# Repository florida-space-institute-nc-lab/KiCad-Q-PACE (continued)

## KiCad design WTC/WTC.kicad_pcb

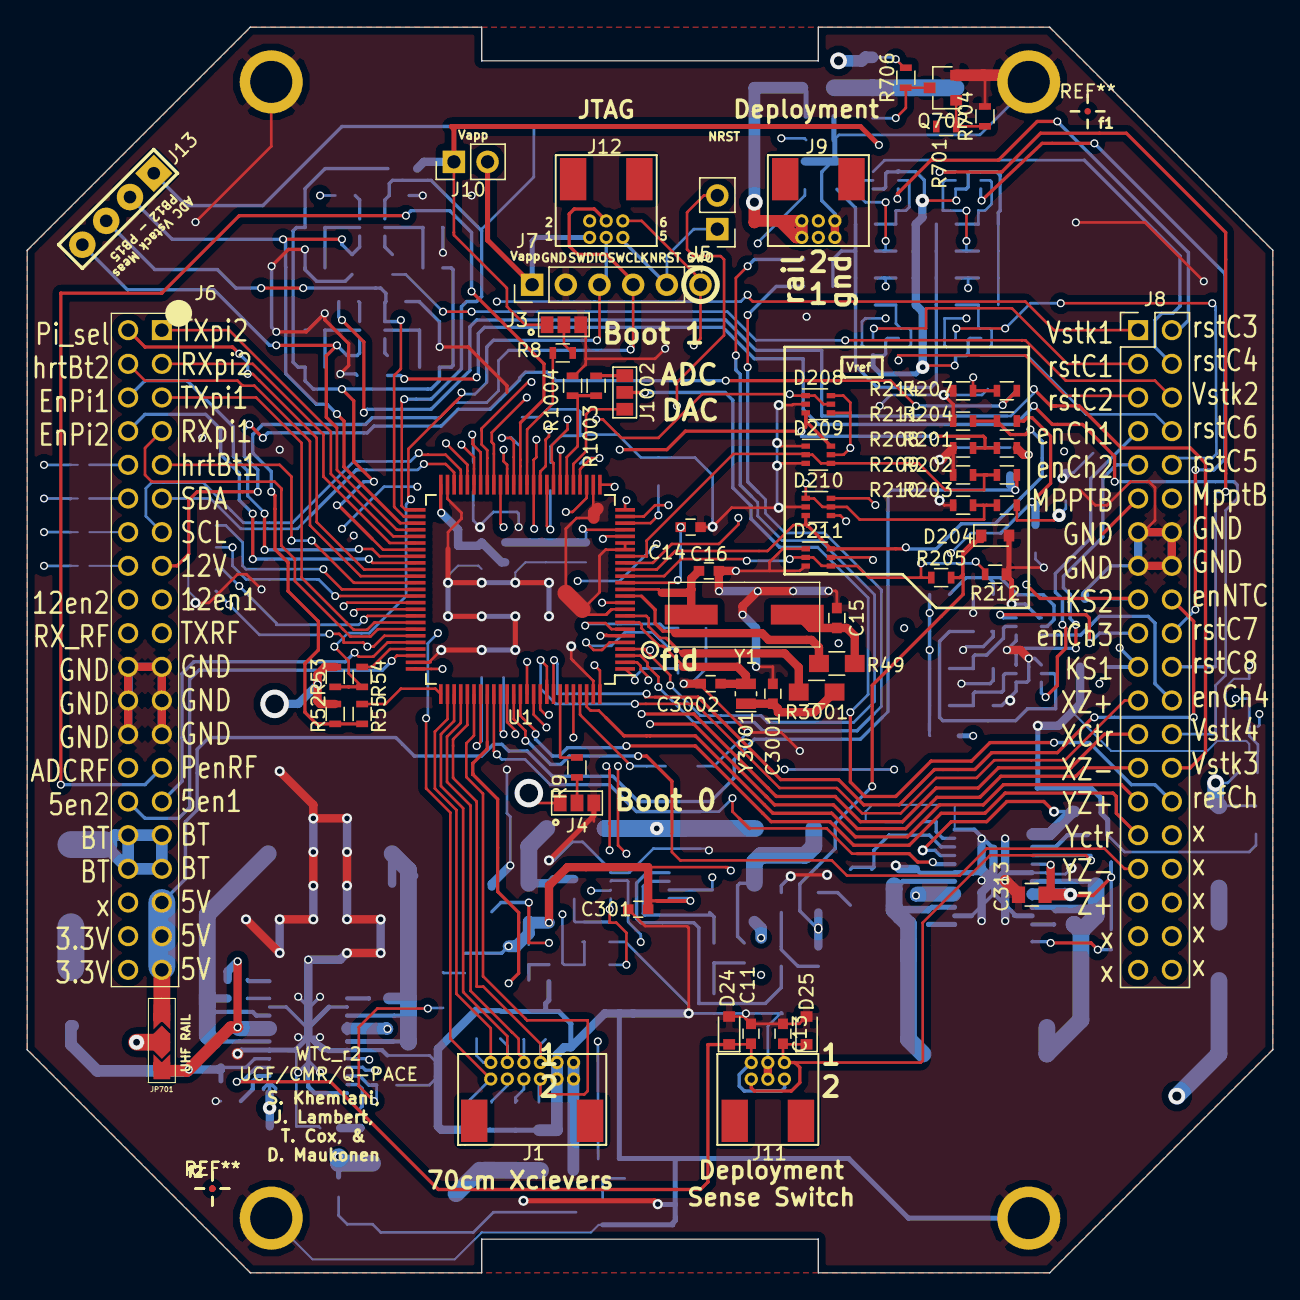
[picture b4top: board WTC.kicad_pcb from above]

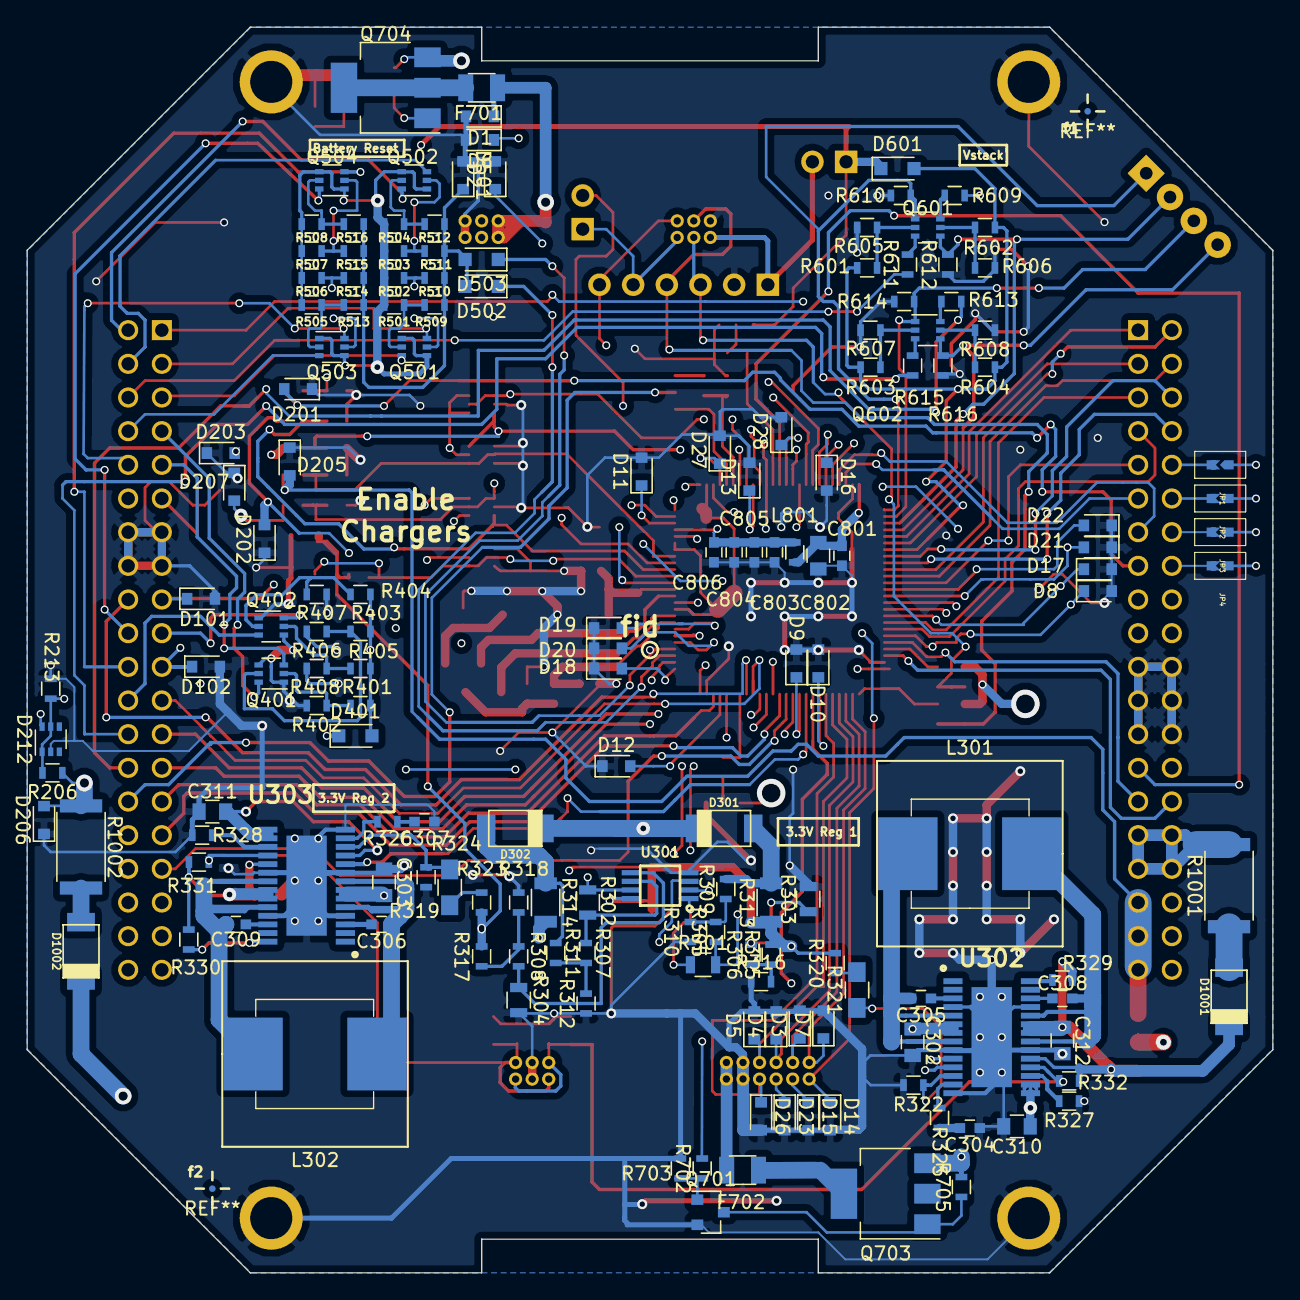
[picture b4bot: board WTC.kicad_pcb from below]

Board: 4 copper layers, 94.0 x 94.0 mm, 227 parts (163 on the bottom side), 190 nets.

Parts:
C11, C13, C14, C301, C305, C306, C308, C309, C801, C804, C805: 0.1 uF; C_0603
C15, C16: 30pF; C_0603
C302, C303, C312, C313: 10 uF; C_0805
C304, C307: 680pF; C_0603
C310, C311: 4.7 uF; C_0805
C802: 1 uF; C_0805
C803: 1 uF; C_0603
C806: 180 pF; C_0603
C3001, C3002: 4.5pF; C_0603
D1, D2, D3, D4, D5, D6, D7, D8, D9, D10, D11, D12, D13, D14, D15, D16, D17, D18, D19, D20, D21, D22, D23, D24, D25, D26, D27, D28, D101, D102, D201, D202, D203, D204, D205, D206, D207, D501: D_TVS_ALT; D_0805
D208, D209, D210, D211, D212: Diode_3_Switching; SOT-363_SC-70-6
D301, D302: D_Schottky_Small; SOD-128
D401, D502, D503, D601: D_Small_ALT; D_SOD-323_HandSoldering
D1001, D1002: D_Schottky_ALT; SOD-128
F701, F702: 3A; Fuse_SMD1206_Reflow
J1: 70cm_Primary; G125-MH11205L3P
J2: Pin_Header_Straight_1x02_Pitch2.54mm
J3: Boot1; GS3
J4: Boot0; GS3
J5: SWD; Pin_Header_Straight_1x01_Pitch2.54mm-rnd
J6: Main 40 Pin Stacking Avionics Interconnect - r 4; Samtec_SSQ-120-03-G-D_QPACE_40-Pin
J7: CONN_01X05; Pin_Header_Straight_1x05_Pitch2.54mm
J8: WTC/MPPT/BP&C_Interconnect_r0; Pin_Header_Straight_2x20_Pitch2.54mm
J9: Deployment; G125-MH10605L3P
J10: CONN_01X02; Pin_Header_Straight_1x02_Pitch2.54mm
J11: CONN_02X03; G125-MH10605L3P
J12: SWD Gecko; G125-MH10605L3P
J13: CONN_01X04; 01x04
J1002: GS3
JP1, JP2, JP3, JP4: SolderBridge_Arrow_small
JP701: UHF Rail Select; SolderBridge_2_way_NP
L301, L302: 3.3 uH; 3.3uH_Dual
L801: Ferrite; L_0603
P3001: Mounting; Mounting_Drill
P3002, P3003, P3004: VAL**; Mounting_Drill
Q401, Q402, Q601, Q602: BSS138_Dual; SOT-363_SC-70-6
Q501, Q502, Q503, Q504: Q_PMOS_SDG_Dual; SOT-363_SC-70-6
Q701, Q702: BSS138; SOT-23
Q703, Q704: Q_PMOS_GDS; SOT-223-3Lead_TabPin2_ONE_2
R8, R9: 100k; R_0603
R49, R319, R321, R3001: 0; R_0805_HandSoldering
R52, R53, R610, R612, R614, R616, R701, R702: 4.99K; R_0603
R54, R55: 51; R_0603
R201, R202, R203, R204, R205, R207, R509, R510, R511, R512, R513, R514, R515, R516, R601, R602, R603, R604: 10K; R_0603
R206: 10M; R_0603
R208: 1k; R_0603
R209: 1K; R_0603
R210, R211, R212: 2.49K; R_0603
R213, R305, R306, R307, R308, R402, R406, R407, R408, R605, R606, R607, R608, R1003, R1004: 1M; R_0603
R214: 523; R_0603
R301, R302, R303, R304: 20M; R_0805
R309, R310, R311, R312, R315, R316, R317, R318: 499K 1%; R_0603
R313, R314: 0.1; R_1206
R320, R323: 352K; R_0603
R322, R324, R329, R330, R331, R332, R401, R403, R404, R405, R501, R502, R503, R504, R505, R506, R507, R508, R703, R704, R705, R706: 100K; R_0603
R325, R326: 78.7K; R_0603
R327, R328: 105K; R_0603
R609, R611, R613, R615: 49.9K; R_0603
R1001, R1002: 0.1; R_2512
U1: STM32L151VE; LQFP-100_14x14mm_Pitch0.5mm
U301: LPV812; VSSOP8_P0.65mm_W3mm
U302, U303: LTC3119; LTC3119_29
Y1: 16 MHz; ECS-160-20-5PXDU-TR_16MHz_Crystal
Y3001: 32.768 KHz; Crystal_SMD_MicroCrystal_CC8V-T1A-2pin_2.0x1.2mm

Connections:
3.3Raw-1: C301.1, C302.1, D202.2, R204.2, R313.1, R315.2, R320.2, U301.8, U302.6, U302.7
3.3Raw-2: C303.2, D204.1, R205.2, R314.1, R317.2, R323.2, U303.6, U303.7
3_3V_Rail: C801.1, C802.1, D207.2, D208.4, D208.6, D209.5, D210.4, D210.6, D211.5, D212.6, D301.1, D302.1, D401.1, D601.1, J3.1, J4.1, J6.38, J6.40, J10.1, L801.2, Q501.1, Q501.4, Q502.1, Q502.4, Q503.1, Q503.4, Q504.1, Q504.4, R52.2, R53.2, R203.2, R501.1, R502.1, R503.1, R504.1, R505.1, R506.1, R507.1, R508.1, U1.6, U1.11, U1.21, U1.28, U1.50, U1.75, U1.100
5V_Rail: D205.2, J6.35, J6.37, J6.39, JP701.1, R202.2
5V_Rail_1_Enable: J6.29, U1.71
5V_Rail_2_Enable: J6.30, U1.73
5X_Out_1: D210.1, D210.5, R203.1, R210.2, U1.17
5X_Out_2: D210.3, D211.6, R204.1, R211.2, U1.16
5X_Out_3: D211.2, D211.4, R205.1, R212.2, U1.15
10X_Out_1: D209.2, D209.4, R202.1, R209.2, U1.18
10X_Out_2: D208.3, D209.6, R201.1, R208.2, U1.32
12V_1_Enable: J6.17, U1.65
12V_2_Enable: J6.18, U1.66
12V_Rail: D201.2, J6.15, R207.2
20X_Out_1: D208.1, D208.5, R207.1, R214.2, U1.33
70cm_AUX_ADC: D14.1, J1.12, U1.41
70cm_AUX_GPIO: D7.1, J1.11, U1.77
70cm_Primary_Enable: D5.1, J1.5, U1.80
70cm_Primary_UART_RX: D4.1, J1.7, U1.79
70cm_Primary_UART_TX: D3.1, J1.9, U1.78
70cm_Secondary_Enable: D26.1, J1.6, U1.81
/Boot0_Sel.: R9.1, U1.94
/JTG1: J7.1, J10.2, J12.1
/JTG3: J7.3, J12.3, R53.1, R54.2
/JTG4: J7.4, J12.4, R52.1, R55.2
/SWCLK: R55.1, U1.76
/SWDIO: R54.1, U1.72
ADC_REF_Chrg: R1003.2, R1004.1, U1.31
Battery_Rail: D203.2, J6.31, J6.32, J6.33, J6.34, Q704.3, R201.2, R706.2, R1001.2
Battery_Reset_1: D502.1, U1.3
Battery_Reset_2: D503.1, U1.4
DAC_REF_Chrg: J1002.1, U1.30
Deployment_Battery_Rail: D1.1, F701.2, J9.1, J9.2
EN_Chrg_1: J8.7, Q401.6
EN_Chrg_2: J8.9, Q401.3
EN_Chrg_3: J8.19, Q402.6
EN_Chrg_4: J8.24, Q402.3
EN_MPPT_XCtr: J8.25, U1.91
EN_MPPT_XZ+: J8.23, U1.92
EN_MPPT_XZ-: J8.27, U1.90
EN_MPPT_YCtr: J8.31, U1.88
EN_MPPT_YZ+: J8.29, U1.98
EN_MPPT_YZ-: J8.33, U1.87
EN_MPPT_Z+: J8.35, U1.86
EN_NTC_Drive: J8.18, U1.93
GND: C11.1, C13.1, C14.2, C15.1, C16.1, C301.2, C302.2, C303.1, C304.2, C307.2, C310.2, C311.2, C312.2, C313.1, C801.2, C802.2, C803.2, C804.2, C805.2, C806.2, C3001.2, C3002.2, D1.2, D2.2, D3.2, D4.2, D5.2, D6.2, D7.2, D8.2, D9.2, D10.2, D11.2, D12.1, D13.2, D14.2, D15.2, D16.2, D17.2, D18.1, D19.1, D20.1, D21.1, D22.1, D23.2, D24.2, D25.2, D26.2, D27.2, D28.2, D101.2, D102.2, D201.1, D202.1, D203.1, D204.2, D205.1, D206.1, D207.1, D208.2, D209.1, D209.3, D210.2, D211.1, D211.3, D212.2, D501.2, J1.3, J1.4, J3.3, J4.3, J6.21, J6.22, J6.23, J6.24, J6.25, J6.26, J7.2, J8.13, J8.14, J8.15, J8.16, J9.5, J9.6, J11.3, J11.4, J12.2, P3001.1, P3002.1, P3003.1, P3004.1, Q401.1, Q401.4, Q402.1, Q402.4, Q701.2, Q702.2, R208.1, R209.1, R210.1, R211.1, R212.1, R213.1, R214.1, R303.2, R304.2, R310.1, R312.1, R316.1, R318.1, R322.1, R324.1, R327.1, R328.1, R402.2, R406.2, R407.2, R408.2, R605.1, R606.1, R607.1, R608.1, R610.1, R612.1, R614.1, R616.1, R703.2, R704.2, R1004.2, U1.10, U1.19, U1.20, U1.27, U1.49, U1.74, U1.99, U301.4, U302.4, U302.9, U302.14, U302.20, U302.25, U302.29, U303.4, U303.9, U303.14, U303.20, U303.25, U303.29
I2C_SCL: J6.13, U1.47
I2C_SDA: J6.11, U1.48
Imon_3.3-1: R301.1, U1.36, U301.1
Imon_3.3-2: R302.1, U1.35, U301.7
Kill_Switch_1: D102.1, J8.21, U1.45
Kill_Switch_2: D101.1, J8.17, U1.46
MPPT_BUS: D206.2, J8.11, J8.12, R206.1, R1002.2
MPPT_BUS_MON: D212.1, D212.5, R206.2, R213.2, U1.24
NRST: J2.1, J7.5, J12.5
unnamed: C14.1, J2.2, U1.14
unnamed: C15.2, R49.2, Y1.1
unnamed: C16.2, U1.13, Y1.2
unnamed: C304.1, R325.1
unnamed: C305.1, U302.3
unnamed: C305.2, L301.1, U302.5, U302.8
unnamed: C306.1, U303.3
unnamed: C306.2, L302.1, U303.5, U303.8
unnamed: C307.1, R326.1
unnamed: C308.1, L301.2, U302.21, U302.24
unnamed: C308.2, U302.26
unnamed: C309.1, L302.2, U303.21, U303.24
unnamed: C309.2, U303.26
unnamed: C310.1, U302.11, U302.15, U302.16
unnamed: C311.1, U303.11, U303.15, U303.16
unnamed: C3001.1, R3001.1, Y3001.1
unnamed: C3002.1, U1.8, Y3001.2
unnamed: D301.2, R309.2, R313.2
unnamed: D302.2, R311.2, R314.2
unnamed: D501.1, D502.2, D503.2, R509.2, R510.2, R511.2, R512.2, R513.2, R514.2, R515.2, R516.2
unnamed: D1001.2, R1001.1
unnamed: D1002.2, R1002.1
unnamed: F701.1, Q704.2
unnamed: F702.1, Q703.2
unnamed: J3.2, R8.2
unnamed: J4.2, R9.2
unnamed: J6.10, JP1.1
unnamed: J6.12, JP2.1
unnamed: J6.14, JP3.1
unnamed: J6.16, JP4.1
unnamed: J5.1, J12.6, U1.89
unnamed: J1002.3, R1003.1
unnamed: JP701.2, Q703.3, R705.1
unnamed: Q401.2, R401.1, R402.1
unnamed: Q401.5, R403.1, R406.1
unnamed: Q402.2, R404.1, R407.1
unnamed: Q402.5, R405.1, R408.1
unnamed: Q501.2, R501.2, R509.1
unnamed: Q501.5, R502.2, R510.1
unnamed: Q502.2, R503.2, R511.1
unnamed: Q502.5, R504.2, R512.1
unnamed: Q503.2, R505.2, R513.1
unnamed: Q503.5, R506.2, R514.1
unnamed: Q504.2, R507.2, R515.1
unnamed: Q504.5, R508.2, R516.1
unnamed: Q601.2, R601.1, R605.2
unnamed: Q601.3, R611.1
unnamed: Q601.5, R602.1, R606.2
unnamed: Q601.6, R609.1
unnamed: Q602.2, R603.1, R607.2
unnamed: Q602.3, R615.1
unnamed: Q602.5, R604.1, R608.2
unnamed: Q602.6, R613.1
unnamed: Q701.1, R702.1, R703.1
unnamed: Q701.3, Q703.1, R705.2
unnamed: Q702.1, R701.1, R704.1
unnamed: Q702.3, Q704.1, R706.1
unnamed: R8.1, U1.37
unnamed: R49.1, U1.12
unnamed: R301.2, R305.2, U301.2
unnamed: R302.2, R307.2, U301.6
unnamed: R303.1, R306.2, U301.3
unnamed: R304.1, R308.2, U301.5
unnamed: R305.1, R309.1, R310.2
unnamed: R306.1, R315.1, R316.2
unnamed: R307.1, R311.1, R312.2
unnamed: R308.1, R317.1, R318.2
unnamed: R319.1, R323.1
unnamed: R319.2, R324.2, U303.12
unnamed: R320.1, R321.2
unnamed: R321.1, R322.2, U302.12
unnamed: R325.2, U302.13
unnamed: R326.2, U303.13
unnamed: R327.2, U302.17
unnamed: R328.2, U303.17
unnamed: R329.2, U302.28
unnamed: R330.2, U303.28
unnamed: R3001.2, U1.9
Pgood_3.3-1: U1.83, U302.10
Pgood_3.3-2: U1.84, U303.10
Pi_Heartbeat_Pi1: J6.9, U1.62
Pi_Heartbeat_Pi2: J6.4, U1.61
PwrMon_RF_ADC: J6.28, U1.40
Pwr_En_Pi1: J6.6, U1.58
Pwr_En_Pi2: J6.8, U1.59
REF_Chrg: J8.30, J1002.2
RF_Deck_Power_Enable: J6.27, U1.38
Reset_C1: J8.3, Q501.6
Reset_C2: J8.5, Q501.3
Reset_C3: J8.2, Q502.6
Reset_C4: J8.4, Q502.3
Reset_C5: J8.10, Q503.6
Reset_C6: J8.8, Q503.3
Reset_C7: J8.20, Q504.6
Reset_C8: J8.22, Q504.3
STM_PA0: D11.1, U1.23
STM_PA4: D27.1, U1.29
STM_PA8: D17.1, JP3.2, U1.67
STM_PA11: D8.1, JP4.2, U1.70
STM_PC5_ADC: D13.1, U1.34
STM_PC6: D22.2, JP1.2, U1.63
STM_PC7: D21.2, JP2.2, U1.64
STM_PC13: D19.2, U1.7
STM_PD1: D10.1, U1.82
STM_PD4: D9.1, U1.85
STM_PE1: D12.2, U1.97
STM_PE2: D18.2, U1.1
STM_PE6: D20.2, U1.5
STM_PE8: D28.1, U1.39
STM_PE13: D16.1, U1.44
Spacecraft_Deployment_Switch_1: C11.2, D24.1, J11.2, J11.5, R332.2, U302.18
Spacecraft_Deployment_Switch_2: C13.2, D25.1, J11.1, J11.6, R331.2, U303.18
UART_RXD_Pi1: J6.7, U1.69
UART_RXD_Pi2: J6.3, U1.56
UART_RX_UHF_Sec: D23.1, J1.8, J6.20, U1.26
UART_TXD_Pi1: J6.5, U1.68
UART_TXD_Pi2: J6.1, U1.55
UART_TX_UHF_Sec: D15.1, J1.10, J6.19, U1.25
UHF_Deploy_1: D2.1, J9.3, U1.43
UHF_Deploy_2: D6.1, J9.4, U1.42
UHF_Power_Enable: R702.2, U1.96
UHF_Rail: F702.2, J1.1, J1.2
UHF_Rail_Raw: C312.1, C313.2, D1001.1, D1002.1, JP701.3, R329.1, R330.1, R331.1, R332.1, U302.19, U302.22, U302.23, U303.19, U303.22, U303.23
VDDA: C803.1, C804.1, C805.1, C806.1, L801.1, U1.22
V_Stack_1: J8.1, R609.2
V_Stack_1_Meas: J13.1, Q601.1, R610.2, U1.51
V_Stack_2: J8.6, R611.2
V_Stack_2_Meas: J13.2, Q601.4, R612.2, U1.53
V_Stack_3: J8.28, R613.2
V_Stack_3_Meas: J13.3, Q602.1, R614.2, U1.52
V_Stack_4: J8.26, R615.2
V_Stack_4_Meas: J13.4, Q602.4, R616.2, U1.54
WTC_BUS_Switch_Pi_Select: J6.2, U1.60
WTC_EN_Chrg: D401.2, R401.2, R403.2, R404.2, R405.2, U1.2
WTC_V_Stack: D601.2, R601.2, R602.2, R603.2, R604.2, U1.57

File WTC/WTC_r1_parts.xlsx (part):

WTC_r2
Ref. | Value | Footprint | Type | Side
C305 | 0.1 uF | Capacitors_SMD:C_0603 | C | bottom
C306 | 0.1 uF | Capacitors_SMD:C_0603 | C | bottom
C308 | 0.1 uF | Capacitors_SMD:C_0603 | C | bottom
C309 | 0.1 uF | Capacitors_SMD:C_0603 | C | bottom
C801 | 0.1 uF | Capacitors_SMD:C_0603 | C | bottom
C804 | 0.1 uF | Capacitors_SMD:C_0603 | C | bottom
C805 | 0.1 uF | Capacitors_SMD:C_0603 | C | bottom
C802 | 1 uF | Capacitors_SMD:C_0805 | C | bottom
C803 | 1 uF | Capacitors_SMD:C_0603 | C | bottom
C302 | 10 uF | Capacitors_SMD:C_0805 | C | bottom
C303 | 10 uF | Capacitors_SMD:C_0805 | C | bottom
C312 | 10 uF | Capacitors_SMD:C_0805 | C | bottom
C806 | 180 pF | Capacitors_SMD:C_0603 | C | bottom
C310 | 4.7 uF | Capacitors_SMD:C_0805 | C | bottom
C311 | 4.7 uF | Capacitors_SMD:C_0805 | C | bottom
C304 | 680pF | Capacitors_SMD:C_0603 | C | bottom
C307 | 680pF | Capacitors_SMD:C_0603 | C | bottom
D502 | 1N4148WS | Footprints:D_SOD-323F-2 | D | bottom
D503 | 1N4148WS | Footprints:D_SOD-323F-2 | D | bottom
D601 | 1N4148WS | Footprints:D_SOD-323F-2 | D | bottom
D212 | BAS16VY,115 | TO_SOT_Packages_SMD:SOT-363_SC-70-6 | D | bottom
D301 | PMEG3050EP,115 | SH_SOD_SON_SOT:SOD-128 | D | bottom
D302 | PMEG3050EP,115 | SH_SOD_SON_SOT:SOD-128 | D | bottom
F701 | 3A / PTTC | Fuse_Holders_and_Fuses:Fuse_SMD1206_Reflow | F | bottom
F702 | 3A / PTTC | Fuse_Holders_and_Fuses:Fuse_SMD1206_Reflow | F | bottom
L301 | DRA125-3R3-R | Footprints:3.3uH_Dual | L | bottom
L302 | DRA125-3R3-R | Footprints:3.3uH_Dual | L | bottom
L801 | MPZ1608S300A | Inductors_SMD:L_0603 | L | bottom
Q701 | BSS138 | TO_SOT_Packages_SMD:SOT-23 | Q | bottom
Q401 | BSS138BKS,115 | TO_SOT_Packages_SMD:SOT-363_SC-70-6 | Q | bottom
Q402 | BSS138BKS,115 | TO_SOT_Packages_SMD:SOT-363_SC-70-6 | Q | bottom
Q601 | BSS138BKS,115 | TO_SOT_Packages_SMD:SOT-363_SC-70-6 | Q | bottom
Q602 | BSS138BKS,115 | TO_SOT_Packages_SMD:SOT-363_SC-70-6 | Q | bottom
Q501 | DMP2200UDW-7 | TO_SOT_Packages_SMD:SOT-363_SC-70-6 | Q | bottom
Q502 | DMP2200UDW-7 | TO_SOT_Packages_SMD:SOT-363_SC-70-6 | Q | bottom
Q503 | DMP2200UDW-7 | TO_SOT_Packages_SMD:SOT-363_SC-70-6 | Q | bottom
Q504 | DMP2200UDW-7 | TO_SOT_Packages_SMD:SOT-363_SC-70-6 | Q | bottom
Q703 | NTF6P02T3G | Footprints:SOT-223-3Lead_TabPin2_ONE_2 | Q | bottom
Q704 | NTF6P02T3G | Footprints:SOT-223-3Lead_TabPin2_ONE_2 | Q | bottom
R319 | 0 | Resistors_SMD:R_0805_HandSoldering | R | bottom
R321 | 0 | Resistors_SMD:R_0805_HandSoldering | R | bottom
R1001 | 0.1 | Resistors_SMD:R_2512 | R | bottom
R1002 | 0.1 | Resistors_SMD:R_2512 | R | bottom
R313 | 0.1 | Resistors_SMD:R_1206 | R | bottom
R314 | 0.1 | Resistors_SMD:R_1206 | R | bottom
R322 | 100K | Resistors_SMD:R_0603 | R | bottom
R324 | 100K | Resistors_SMD:R_0603 | R | bottom
R329 | 100K | Resistors_SMD:R_0603 | R | bottom
R330 | 100K | Resistors_SMD:R_0603 | R | bottom
R331 | 100K | Resistors_SMD:R_0603 | R | bottom
R332 | 100K | Resistors_SMD:R_0603 | R | bottom
R401 | 100K | Resistors_SMD:R_0603 | R | bottom
R403 | 100K | Resistors_SMD:R_0603 | R | bottom
R404 | 100K | Resistors_SMD:R_0603 | R | bottom
R405 | 100K | Resistors_SMD:R_0603 | R | bottom
R501 | 100K | Resistors_SMD:R_0603 | R | bottom
R502 | 100K | Resistors_SMD:R_0603 | R | bottom
R503 | 100K | Resistors_SMD:R_0603 | R | bottom
R504 | 100K | Resistors_SMD:R_0603 | R | bottom
R505 | 100K | Resistors_SMD:R_0603 | R | bottom
R506 | 100K | Resistors_SMD:R_0603 | R | bottom
R507 | 100K | Resistors_SMD:R_0603 | R | bottom
R508 | 100K | Resistors_SMD:R_0603 | R | bottom
R703 | 100K | Resistors_SMD:R_0603 | R | bottom
R705 | 100K | Resistors_SMD:R_0603 | R | bottom
R327 | 105K | Resistors_SMD:R_0603 | R | bottom
R328 | 105K | Resistors_SMD:R_0603 | R | bottom
R509 | 10K | Resistors_SMD:R_0603 | R | bottom
R510 | 10K | Resistors_SMD:R_0603 | R | bottom
R511 | 10K | Resistors_SMD:R_0603 | R | bottom
R512 | 10K | Resistors_SMD:R_0603 | R | bottom
R513 | 10K | Resistors_SMD:R_0603 | R | bottom
R514 | 10K | Resistors_SMD:R_0603 | R | bottom
R515 | 10K | Resistors_SMD:R_0603 | R | bottom
R516 | 10K | Resistors_SMD:R_0603 | R | bottom
R601 | 10K | Resistors_SMD:R_0603 | R | bottom
R602 | 10K | Resistors_SMD:R_0603 | R | bottom
R603 | 10K | Resistors_SMD:R_0603 | R | bottom
R604 | 10K | Resistors_SMD:R_0603 | R | bottom
R206 | 10M | Resistors_SMD:R_0603 | R | bottom
R213 | 1M | Resistors_SMD:R_0603 | R | bottom
R305 | 1M | Resistors_SMD:R_0603 | R | bottom
R306 | 1M | Resistors_SMD:R_0603 | R | bottom
R307 | 1M | Resistors_SMD:R_0603 | R | bottom
R308 | 1M | Resistors_SMD:R_0603 | R | bottom
R402 | 1M | Resistors_SMD:R_0603 | R | bottom
R406 | 1M | Resistors_SMD:R_0603 | R | bottom
R407 | 1M | Resistors_SMD:R_0603 | R | bottom
R408 | 1M | Resistors_SMD:R_0603 | R | bottom
R605 | 1M | Resistors_SMD:R_0603 | R | bottom
R606 | 1M | Resistors_SMD:R_0603 | R | bottom
R607 | 1M | Resistors_SMD:R_0603 | R | bottom
R608 | 1M | Resistors_SMD:R_0603 | R | bottom
R301 | 20M | Resistors_SMD:R_0805 | R | bottom
R302 | 20M | Resistors_SMD:R_0805 | R | bottom
R303 | 20M | Resistors_SMD:R_0805 | R | bottom
R304 | 20M | Resistors_SMD:R_0805 | R | bottom
R320 | 352K | Resistors_SMD:R_0603 | R | bottom
R323 | 352K | Resistors_SMD:R_0603 | R | bottom
R610 | 4.99K | Resistors_SMD:R_0603 | R | bottom
R612 | 4.99K | Resistors_SMD:R_0603 | R | bottom
R614 | 4.99K | Resistors_SMD:R_0603 | R | bottom
R616 | 4.99K | Resistors_SMD:R_0603 | R | bottom
R702 | 4.99K | Resistors_SMD:R_0603 | R | bottom
R609 | 49.9K | Resistors_SMD:R_0603 | R | bottom
R611 | 49.9K | Resistors_SMD:R_0603 | R | bottom
R613 | 49.9K | Resistors_SMD:R_0603 | R | bottom
R615 | 49.9K | Resistors_SMD:R_0603 | R | bottom
R309 | 499K 1% | Resistors_SMD:R_0603 | R | bottom
R310 | 499K 1% | Resistors_SMD:R_0603 | R | bottom
R311 | 499K 1% | Resistors_SMD:R_0603 | R | bottom
R312 | 499K 1% | Resistors_SMD:R_0603 | R | bottom
R315 | 499K 1% | Resistors_SMD:R_0603 | R | bottom
R316 | 499K 1% | Resistors_SMD:R_0603 | R | bottom
R317 | 499K 1% | Resistors_SMD:R_0603 | R | bottom
R318 | 499K 1% | Resistors_SMD:R_0603 | R | bottom
R325 | 78.7K | Resistors_SMD:R_0603 | R | bottom
R326 | 78.7K | Resistors_SMD:R_0603 | R | bottom
U301 | LPV812DGKR | Footprints:VSSOP8_P0.65mm_W3mm | U | bottom
U302 | LTC3119 | Footprints:LTC3119_29 | U | bottom
U303 | LTC3119 | Footprints:LTC3119_29 | U | bottom
C11 | 0.1 uF | Capacitors_SMD:C_0603 | C | top
C13 | 0.1 uF | Capacitors_SMD:C_0603 | C | top
C14 | 0.1 uF | Capacitors_SMD:C_0603 | C | top
C301 | 0.1 uF | Capacitors_SMD:C_0603 | C | top
C313 | 10 uF | Capacitors_SMD:C_0805 | C | top
C15 | 30pF | Capacitors_SMD:C_0603 | C | top
C16 | 30pF | Capacitors_SMD:C_0603 | C | top
C3001 | 4.5pF | Capacitors_SMD:C_0603 | C | top
C3002 | 4.5pF | Capacitors_SMD:C_0603 | C | top
D208 | BAS16VY,115 | TO_SOT_Packages_SMD:SOT-363_SC-70-6 | D | top
D209 | BAS16VY,115 | TO_SOT_Packages_SMD:SOT-363_SC-70-6 | D | top
D210 | BAS16VY,115 | TO_SOT_Packages_SMD:SOT-363_SC-70-6 | D | top
D211 | BAS16VY,115 | TO_SOT_Packages_SMD:SOT-363_SC-70-6 | D | top
Q702 | BSS138 | TO_SOT_Packages_SMD:SOT-23 | Q | top
R3001 | 0 | Resistors_SMD:R_0805_HandSoldering | R | top
R49 | 0 | Resistors_SMD:R_0805_HandSoldering | R | top
R54 | 51 | Resistors_SMD:R_0603 | R | top
R55 | 51 | Resistors_SMD:R_0603 | R | top
R214 | 523 | Resistors_SMD:R_0603 | R | top
R704 | 100K | Resistors_SMD:R_0603 | R | top
R706 | 100K | Resistors_SMD:R_0603 | R | top
R8 | 100k | Resistors_SMD:R_0603 | R | top
R9 | 100k | Resistors_SMD:R_0603 | R | top
R201 | 10K | Resistors_SMD:R_0603 | R | top
R202 | 10K | Resistors_SMD:R_0603 | R | top
R203 | 10K | Resistors_SMD:R_0603 | R | top
R204 | 10K | Resistors_SMD:R_0603 | R | top
R205 | 10K | Resistors_SMD:R_0603 | R | top
R207 | 10K | Resistors_SMD:R_0603 | R | top
R208 | 1k | Resistors_SMD:R_0603 | R | top
R209 | 1K | Resistors_SMD:R_0603 | R | top
R1003 | 1M | Resistors_SMD:R_0603 | R | top
R1004 | 1M | Resistors_SMD:R_0603 | R | top
R210 | 2.49K | Resistors_SMD:R_0603 | R | top
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
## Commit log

2019-03-07 added upper part of avionics stack
2019-03-07 initial commit development board
2019-03-08 main sheets created
2019-03-09 added FTDI
2019-03-09 added extra USB port, gyroscope, stack connector
    Much more work needs to be done. almost all high level sheets are made
2019-03-10 added KISS description, UART-I2C chip
    keep it simple, stupid. Goal is to create software development board for sub-system comms
2019-03-11 reduced complexity
2019-04-23 Q-PACE Devboard V0
    This should complete the KiCad Schematic and PCB files. Parts should be in FSI inventory.
2019-04-23 added silk screen, organized pins
2019-04-23 fixed silk screen
2019-04-29 ready for production
    passed all KiCad error checking. schematic and pcblayout were both validated. ready to be ordered
2019-04-29 cleaned up directory / generated production files
2019-04-29 added Gerber zip and images
2019-05-07 added resistor calculator for MP1584 DC-DC converter
    resistor values for 3.3V and 5.0V
